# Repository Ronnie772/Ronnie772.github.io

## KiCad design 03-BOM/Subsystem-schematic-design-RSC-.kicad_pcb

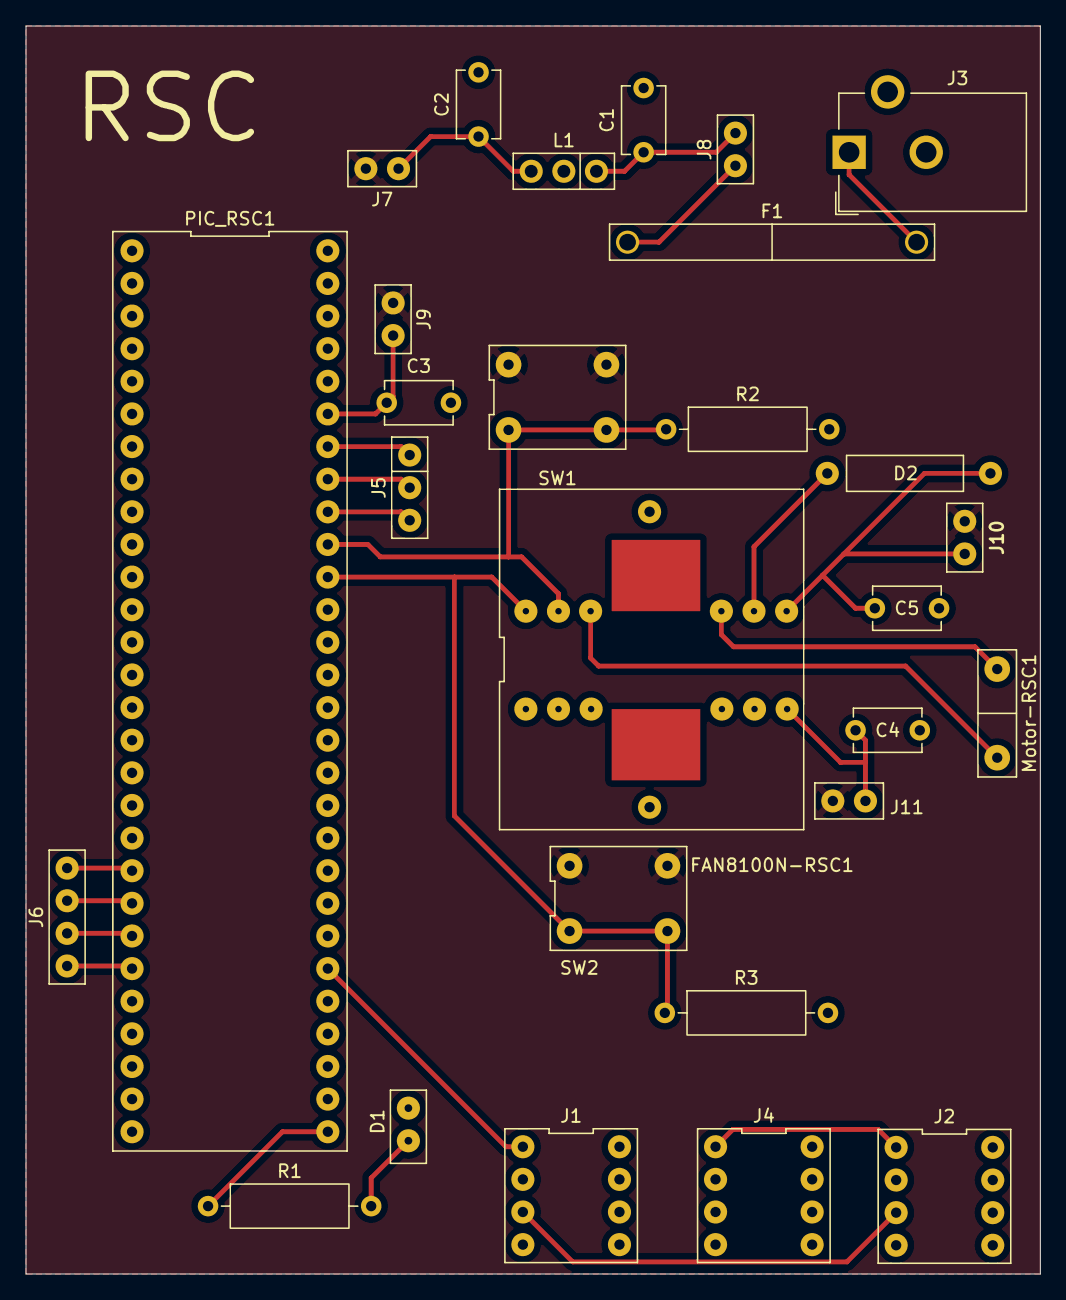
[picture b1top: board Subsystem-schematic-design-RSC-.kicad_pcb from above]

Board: 2 copper layers, 79.0 x 97.2 mm, 28 parts (0 on the bottom side), 26 nets.

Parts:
C1: .33uF; C_Disc_D5.1mm_W3.2mm_P5.00mm
C2: .1uF; C_Disc_D5.1mm_W3.2mm_P5.00mm
C3: 1uF; C_Disc_D5.1mm_W3.2mm_P5.00mm
C4, C5: 0.1uF; C_Disc_D5.1mm_W3.2mm_P5.00mm
D1: LED - RED; LED-RSC
D2: D_Small; Diode-RSC(egr304)
F1: 1500mA; fuse-RSC(4628 - Keystone Electronics)
FAN8100N-RSC1: FAN8100N - RSC
J1, J2, J4: Conn_02x04_Odd_Even; 8_pin_ribbon_connector
J3: Barrel_Jack_Switch_RSC; BarrelJack_CUI_PJ-102AH_Horizontal
J5: Conn_01x03; conn_01x03-RSC
J6: Conn_01x04; conn_01x04-RSC
J7, J8, J9, J10, J11: Conn_01x02; header-RSC(egr304)
L1: LM7805_RSC; LM7805T - RSC
Motor-RSC1: MOTOR-RSC(egr304)
PIC_RSC1: Microchip-PIC18F57Q43-RSC
R1: 220 - 1/4W; R_Axial_DIN0309_L9.0mm_D3.2mm_P12.70mm_Horizontal
R2, R3: 10k - 2.5mW; R_Axial_DIN0309_L9.0mm_D3.2mm_P12.70mm_Horizontal
SW1, SW2: SW_DPST; switch-RSC(egr304)

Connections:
+5V: J7.1, J9.2, J10.1, J11.2, SW1.2, SW1.4, SW2.2, SW2.4
+9V: C1.1, J8.1, L1.1 (input)
/FWD: FAN8100N-RSC1.11 (FORWARDA), PIC_RSC1.47 (RB3), R2.1, SW1.1, SW1.3
/HIGH/LOW: J1.1, PIC_RSC1.34 (RF4)
/Low Light Signal: J2.1, J4.1
/REV: FAN8100N-RSC1.12 (REVERSEA), PIC_RSC1.46 (RB0), R3.1, SW2.1, SW2.3
/STATUS: J1.5, J2.5
/open analog pin (RA5): J5.3, PIC_RSC1.48 (RA5)
/open analog pin (RA6): J5.2, PIC_RSC1.49 (RA6)
/open analog pin (RA7): J5.1, PIC_RSC1.50 (RA7)
/open digital pin (RD0): J6.1, PIC_RSC1.20 (RD0)
/open digital pin (RD1): J6.2, PIC_RSC1.21 (RD1)
/open digital pin (RD2): J6.3, PIC_RSC1.22 (RD2)
/open digital pin (RD3): J6.4, PIC_RSC1.23 (RD3)
GNDREF: C1.2, C2.2, C3.2, C4.2, C5.2, D1.1 (K), FAN8100N-RSC1.FIN (GND), FAN8100N-RSC1.FIN2, J1.8, J2.8, J3.2, J4.8, L1.2 (ground), PIC_RSC1.15 (GND), PIC_RSC1.33 (GND), PIC_RSC1.42 (GND), PIC_RSC1.52 (GND), PIC_RSC1.55 (VOFF), R2.2, R3.2
unnamed: D1.2 (A), R1.2
unnamed: C5.1, D2.2 (A), FAN8100N-RSC1.7 (D1A), J10.2
unnamed: D2.1 (K), FAN8100N-RSC1.8 (PVCCA)
unnamed: F1.1, J3.1
unnamed: FAN8100N-RSC1.9 (OUT1A), Motor-RSC1.2 (-)
unnamed: FAN8100N-RSC1.10 (OUT2A), Motor-RSC1.1 (+)
unnamed: C4.1, FAN8100N-RSC1.6 (VCC), J11.1
unnamed: C2.1, J7.2, L1.3 (output)
unnamed: F1.2, J8.2
unnamed: C3.1, J9.1, PIC_RSC1.51 (VTG)
unnamed: PIC_RSC1.29 (RC0), R1.1

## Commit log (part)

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2025-10-21 deploy: 94ea3dc490fe3c758b65137d5e656e37ea6d8cf4
2025-10-21 deploy: 77847a24be2f510384c50da9603a9fab1be8f9ff
2025-10-21 deploy: 31c2d7407d839f5fb5cd9afea95ae7eff579f542
2025-10-21 deploy: 19ba6eb65b591dec3645b0af00fd187877fe23e9
2025-10-21 deploy: 9a129213dec03510292066d42e95b81775c423f4
2025-10-21 deploy: 2a9ff8a27a6ef622951778c1e0886a1338ee2274
2025-10-21 deploy: d546716491812ce638b132b2e63a17a4662f432a
2025-10-21 deploy: 90f42e284099315b2296821cf1c3f0b41deb0d6b
2025-10-21 deploy: 3735dc83b4c405a99cfee07080c969a65475ee14
2025-10-21 deploy: 43c31c52bc6c8176fa1868e490747df0dc20c863
2025-10-22 deploy: 94689fe791fbb98ecbeee8bf243cb28862caa4fe
2025-10-22 deploy: 479015b89c009d1b9168bd64664944df048f2309
2025-10-22 deploy: 9b9eaf022edda0c1ed8ebe87b8603e35eb9ee916
2025-10-22 deploy: fa679af43ae199ebd3b6319ba6b44c5fa8b6b803
2025-10-22 deploy: 1613349a56264152ecccf2072141d60a9560daed
2025-10-22 deploy: 918b6e19f5c59687fe8eab75dc851c97f2979775
2025-10-22 deploy: 3bbbecca2e3e0ef9387ea575fc771c0f26b2f8fa
2025-10-22 deploy: fad791e16f7e751dc8595d80ba99aee682101261
2025-10-23 deploy: e5d9cd6d5b54ec6de9a05834efc3d38269d19918
2025-10-23 deploy: ec6b087709484f1650c6395c6e923b334f2e0edc
2025-10-23 deploy: 6b32b24c827aa2ecd9a7928b597e274c4490ff5c
2025-10-23 deploy: 404c881eaced70a2a79dbb3e75c7ea7155ddea92
2025-10-23 deploy: a9ecdfac2184401c40bc913caca920f771f9dfbb
2025-10-27 deploy: 07639fec88c5482e6656d202e2b064fd5fbec17d
2025-10-27 deploy: 1da612bfaaf56832e5c16b66372adb89269b6377
2025-10-27 deploy: b194877f3d4db3785da0c406734eb5fa971befc6
2025-10-27 deploy: 6ee2e39b19b071c2922fe779079f653b55c0429d
2025-10-27 deploy: 520d39ef1a33c1564ca450b8aad84c2dba751321
2025-10-27 deploy: 8487e31c7cb9261f8fc0a6c2eb716d32d77c7138
2025-10-27 deploy: 6ba6d365b4cfaafac41cc0b3701be5d58e349104
2025-10-27 deploy: ba252a613dd84521e7df9cede8e331fefcb4a4f5
2025-10-27 deploy: fa965202bdc1f8408d9dbc3820c29bc676db421e
2025-10-27 deploy: 48080ba564e8245d846660ebc01dffeecc0c953b
2025-10-27 deploy: c4691c835f333bb65ccd7b42729d1c032f8241c9
2025-10-27 deploy: 17226ad6f3f10517ab3fbe01bb8bb6bba9c731e5
2025-10-27 deploy: e8e29434313e9c6eb443b76e3b1b3ed9f8fb8d6b
2025-10-27 deploy: b1470108e278f7ac6437be2777c3be60a17f685e
2025-10-27 deploy: bd8e418ae1785c8cb99e468149a24bbe13c1d4f1
2025-10-27 deploy: 2fb0828682be2c3ebfc88eb02bd23ca67fbaf00e
2025-10-27 deploy: 910c5d34a6157dc1030761fe27847041718eab19
2025-10-30 deploy: 535bc13348f05ccd73e2e515310352a2fa412a2d
2025-10-30 deploy: d7c08d58749b1838efd854fe188df04e01407261
2025-10-30 deploy: 3a1509915377274ee1f1ea46c58c8d86fabc6045
2025-10-30 deploy: f61e8bb7173d4b017dcfa752fa5f30935be259ae
2025-11-01 deploy: 41eae30fc687ed11f28421b2a29c6cba351b1ab9
2025-11-01 deploy: 1ddc824f9cb8dfa4fc0440e892c7661e3fa5c9be
2025-11-01 deploy: 5cb344e156b365bab8231950f3a945210d4d1460
2025-11-01 deploy: 1008796bf824af37dc262a36bf020a57f9bf2789
2025-11-01 deploy: 04f03f46834bb7e34a471b03610cd668ce391987
2025-11-01 deploy: f5d6d3c765302c7f9bfa5f9fdc78d7850fd69fbe
2025-11-01 deploy: 22f37aa86536a165aed445d3b3098ced04205fde
2025-11-01 deploy: 1c5024a673f7486d560245ce26a4be8cdf9078d2
2025-11-01 deploy: 652df0c911501b775f37b4559ee6dc61f062dccc
2025-11-02 deploy: 69f786417133d73180760f2c1c029ce889b1aeee
2025-11-02 deploy: 267ce65cf3d3016423c508b7bd00fcbfac862e2a
2025-11-02 deploy: 626327625fb3c9ac1062a27d136cfc25e08bcf6e
2025-11-06 deploy: d12b423de0a9b79f093e16f45f86f0c3a822227b
2025-11-06 deploy: 874fc954c364bbdc2124e9ecdbd935da2ad4e7cb
2025-11-06 deploy: 334b9ee721c8055dc03312374716d438eeb7657d
2025-11-06 deploy: ae0ffeed86faaac51cd98249b306d18852d2f66d
2025-11-07 deploy: 75628c107cc4bf3d6b8cc87f23a4b623808a7e51
2025-11-07 deploy: c1ed85f78ea8b302c0d8cec0b001a60ca08f53e8
2025-11-08 deploy: 1055fbd3c175ffca6ba85392d28a36d0ed25d896
2025-11-08 Create 06-PCB
2025-11-10 deploy: 825ccebe6dfc4c9468d72bfd51fd31bf90b697bb
2025-11-10 deploy: e729f862ed8d1d7053630886d54c836b8965adb1
2025-11-10 deploy: adf906e0ff3a75300743e8b7373faf156ca6f475
2025-11-10 deploy: 3e9482bfcfd83fd4c2b1567c32334f4fff0aaa20
2025-11-10 deploy: 42a33aaee7d14be63818dd11e0a72babed381dc1
2025-11-10 Rename docs/06-PCB-Design.md to docs/06-PCB-Design/06-PCB-Design.mb
2025-11-10 deploy: 4b58efe7baee27d788f06ac163b108b31c1906d1
2025-11-10 deploy: 5be0285cca00c51eaafb87f6fc7c0fecc2d8dbfe
2025-11-10 deploy: 1c7f7c1afc504a4d53092665fa87a645e089baf9
2025-11-10 deploy: f1cf325c145b0a8b259d50c04191bf0940b8a7b2
2025-11-10 deploy: 1dfd0e7f1de0e142d6b914a7f90d6f0d2f3941a4
2025-11-10 deploy: 073c1113caa579d7d767bcc42a99e7a22cd89e8f
2025-11-10 deploy: bf11379073cec723843a26548c49105e505982cc
2025-11-11 deploy: ef3f3ddcb27ff3ab5e77ea5f7e87f4894c7cd1da
2025-11-11 deploy: bf5486ac216e9bacd1637cb09dd8026a932089e3
2025-11-11 deploy: d9f3778cce25e5f7cfa44754258d04aa7c5f6db3
2025-12-01 Update schematic image and resources links
    Updated the schematic image and corrected the PDF link.
2025-12-01 deploy: ff00160655c3062cbacaa84d43d3aed50854549c
2025-12-04 deploy: a83db6e46ef011a3d46702938161d370e222a44a
2025-12-04 Update Code.md with title and overview
    Added title and overview section to Code.md
2025-12-04 Refine comments in motor control code
    Updated comments for clarity in motor control logic.
2025-12-04 deploy: 0145c80de49e235799c16e1628d58ae12c33ed03
2025-12-04 Fix formatting issues in Code.md
2025-12-04 Refactor code structure in Code.md
    Reorganize includes and defines for clarity.
2025-12-04 Fix formatting and clean up comments in Code.md
2025-12-04 deploy: 57e00e260b7f9c0c57b42b80de61f9b2fb47266c
2025-12-04 Modify PCB design documentation
    Updated PCB design documentation with new image and corrected resource links.
2025-12-04 deploy: 8df3b84b3f6585dd37fb24d79401cc274d683292
2025-12-06 deploy: 9cc0768d7dab6c53dc100d1cbec34122200d29f0
2025-12-06 Replace BOM image and add XLSX file link
    Updated the BOM image and added a link to the XLSX file.
2025-12-06 deploy: 3ab3c6070c13089d2171f105e13de8fa377b3776
2025-12-06 deploy: ca8517c9bf68caa3c1b210bb071ab3b5292ace6d
2025-12-07 Update index.md with team member links
    Added team member datasheet links to the documentation.
2025-12-07 Update submission date from OCT to DEC 2025
2025-12-07 deploy: ccef9fc0d7a7831e204b2f5128be1cb478a5ec3e
2025-12-07 Fix typos and improve formatting in index.md
    Corrected typos and formatting issues in the project summary and contribution sections.
2025-12-07 deploy: 5c3f58ae4c86fed2f1c69f0d0be824749cfdae52
2025-12-07 deploy: f03c0ac9fbc378a14783ec8afb5a24b24fe653ea
2025-12-08 Refine rationales for component selections
    Updated rationales for component selections to provide more detail on efficiency, cost savings, and suitability for requirements.
2025-12-08 deploy: dbde22f08b0d3418bacd04b7cd1f801d99135b64
2025-12-09 Enhance overview of motor subsystem block diagram
    Expanded the overview section to include details about the power supply, microcontroller functionality, PWM control, override switches, and H-bridge operation for the motor subsystem.
2025-12-09 deploy: a76ce6c6a3517d304213a6c3e5ab351cf8b3df0d
2025-12-09 deploy: a857b4540aed91ac09ceda723dc04b5e7745c1cd
2025-12-09 Add H-Bridge and Motor to component selection table
2025-12-09 Update rationale for component PJ-102AH
2025-12-09 deploy: a5cbe2626639516d1f7650252b46d1697156d8c4
2025-12-09 deploy: 12727ae705234ac192813641ed4eacb958263307
2025-12-09 deploy: 8cbc2619be6ee824c3502714554b0d8adb923fe8
2025-12-09 deploy: 9ab31fc2119f90e056f30645821287d0bda7543b
2025-12-09 Correct Excel sheet link in Power Budget document
    Fix markdown link formatting for Excel sheet.
2025-12-09 Fix link formatting in Power-Budget.md
2025-12-09 deploy: a3badda52a71661a2546886cb1a28f43d934795b
2025-12-09 Update BOM overview with cost and sourcing details
    Expanded the overview section to include total cost and sourcing information for the motor subsystem.
2025-12-09 deploy: 4e168efa5fc9aa7ffbfb90bdb86928915cb4e8fa
2025-12-09 deploy: 05c41c4757525e6c0422da8e022d9172604184e5
2025-12-09 Enhance Power Budget documentation with component details
    Added details on component specifications and safety margins for the motor subsystem's power budget.
2025-12-09 Update PCB design documentation with images and resources
    Added images of the PCB design before and after soldering, along with resource links for gbr and ecad project files.
2025-12-09 deploy: 3f5621bb2f400b481c556460a98a9d8035b34825
2025-12-09 Update PCB design documentation for partial soldering
2025-12-09 Fix typos and enhance clarity in PCB design doc
    Corrected minor typos and improved clarity in the PCB design documentation.
2025-12-09 deploy: 07a85a46cf01dff975ffe618a00d14c103674a7d
2025-12-09 deploy: 49ede33d7acd84d0bb93c45da7b9011c27bec3b3
2025-12-09 deploy: 4bc2959bd8d184de23dbc519b3553d8fc15a7bb4
2025-12-09 deploy: d83833a7e6a47380adf86aedd22ba2b342949d83
2025-12-09 Include link to MPLab project .zip
    Added a link to the MPLab project .zip file.
2025-12-09 deploy: 6ba0caad862a24bca1da28183c5b16bb923b8702
2025-12-09 Fix spelling errors and format improvement list
    Correct spelling errors and reformat improvements for clarity.
2025-12-09 deploy: cb9a80cd06385f4f4f0b241fc222f84f1297dc89
2025-12-09 Improve formatting of hardware improvements section
    Formatted improvement points for better readability.
2025-12-09 deploy: aeda3e33ac9f76d27dc1c1f5950defa0109b4d57
2025-12-09 deploy: 49bfe2ddea8b55d36266b446f1af579af72255ad
2025-12-09 deploy: 8fca65fb82af5bf064f5df1bdf0ae20221e46242
2025-12-09 Format improvements in hardware documentation
2025-12-09 deploy: cb7ad840bf14ce4e63024ebd58e99adc81aa5434
2025-12-09 deploy: 35f3a546663748428278e061c4180197c59bec81
2025-12-09 Fix formatting and improve clarity in hardware documentation
2025-12-09 Fix spelling errors in motor subsystem overview
    Corrected spelling errors in the overview section.
2025-12-09 deploy: db306492e72359c0d2051169bd2bb3d5554d6ea5
2025-12-09 deploy: 5d9886947b28663841d01bceeed3cac13f4b6927
2025-12-09 Revise overview for Hardware V2.0 documentation
    Updated the overview section to clarify the goals and improvements of Hardware V2.0.
2025-12-09 deploy: dfce12e7e539e2af3070b7644d23b9c8c1a838f7
2025-12-09 Enhance Resources section with design documentation details
    Added detailed explanation of resources for motor subsystem development.
2025-12-09 deploy: 390442df0723c2245ff4c495aa9cec4046fc7b47
2025-12-09 deploy: a8269eaa36e6e3312069f57d78507774938608fa
2025-12-09 deploy: 9d5abaac05fef427977c4020b698f30932e43dcd
2025-12-09 deploy: 8fe1358aa982a13838fcc7d45db71a60c190c715
2025-12-09 deploy: 54aa56e039d1bdf044e8190bf7050ecfb394ae90
2025-12-09 deploy: 88db76236fde8393bb2ff554f934f92b22bfd142
2025-12-09 deploy: f8b4b29d700f290e6902d78d94883975f0c18243
2025-12-09 deploy: 0f4159c09f03a727cff13c47161d4c8483c58dae
2025-12-09 deploy: 5a049ab3c9628abefb4ce61c844bbb016986c8ac
2025-12-09 deploy: 55de1c36ac6ae935cc62cd27469cad4d4e5cdcfa
2025-12-09 deploy: 5684f042587fa04aca3b6727a5035b002ac0d0ad
2025-12-09 deploy: a16e7737131d5e4ef6e7221ac9e4a925375334b2
2025-12-09 deploy: 853a4dd1ae403b24ecc33b94cba4cb8775d21552
2025-12-09 deploy: 363d40186c104f2a9df4e0d05c1b7c82fb689cdb
2025-12-09 deploy: 960bc3f6c5ba50764938993d98acbd0ad2f4a6a8
2025-12-09 deploy: 7e24117ff2b96773f78a2ba9d0d593f3a0b05f96
2025-12-09 deploy: 98c6c9e0a88855ecd933b90fdf222f50d2dbcf46
2025-12-09 deploy: d3b8236e395dc79a3897c09606baff289a9c78d6
2025-12-09 deploy: 6366f55fc0c508c1e5630669fb0c9194a8a9de48
2025-12-09 deploy: 6276fc08767bd87634df979149e1d0d9f60320dc
2025-12-09 deploy: 2ab90ac5a06d5b85312851e325bfac6938152295
2025-12-09 deploy: 2c5d4ed9bf5ad54627e1becf00570a13f9917705
2025-12-09 deploy: 46646de074850c82b7759507c32dc1204caceaf1
2025-12-09 deploy: b9afdb3a20f257d4245d71e1ab052ec519750dda
2025-12-09 deploy: 1a041726fc622d8c845a9d1c41abdef283219c64
2025-12-09 deploy: a6188602cbfe5c96f12cf07bc50e1527b57a1e60
2025-12-09 deploy: 62d9ae6b0b8abc244a927586d7f39760c237793d
